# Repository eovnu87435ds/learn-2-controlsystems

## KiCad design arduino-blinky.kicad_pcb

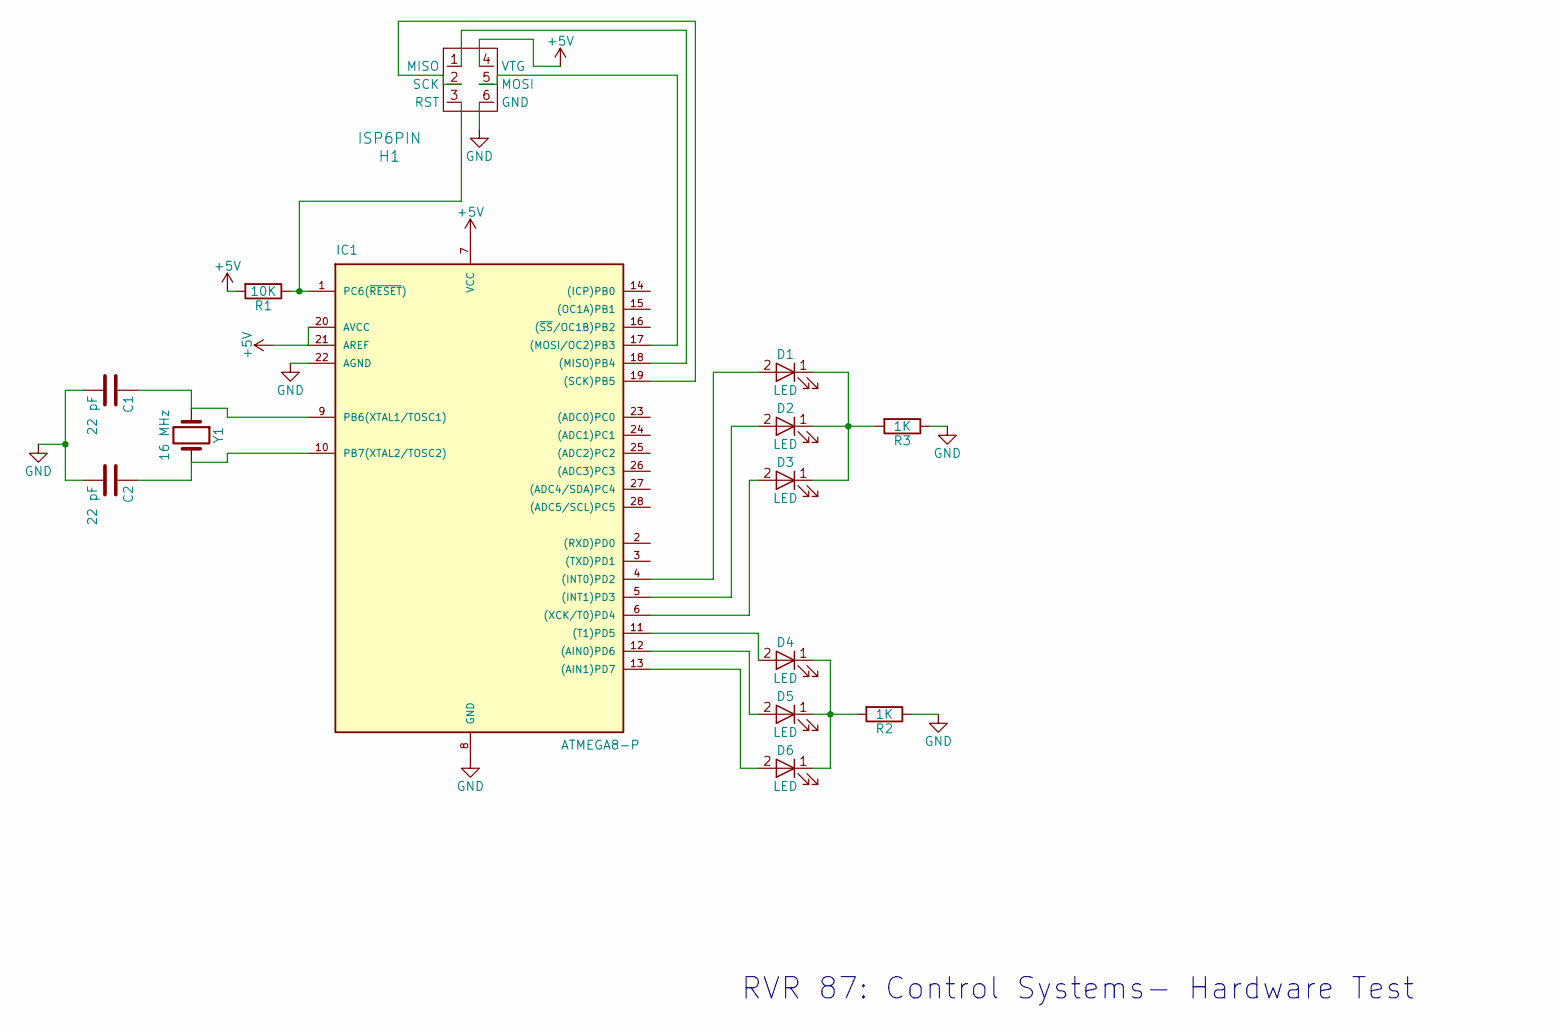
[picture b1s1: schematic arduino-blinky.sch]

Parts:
C1, C2: 22 pF; C_Disc_D3.0mm_W2.0mm_P2.50mm
D1, D2, D3, D4, D5, D6: LED; LED_D3.0mm
H1: ISP6PIN
IC1: ATMEGA8-P; DIP-28_W7.62mm_Socket
R1: 10K; R_Axial_DIN0309_L9.0mm_D3.2mm_P12.70mm_Horizontal
R2, R3: 1K; R_Axial_DIN0309_L9.0mm_D3.2mm_P12.70mm_Horizontal
Y1: 16 MHz; Crystal_HC18-U_Vertical

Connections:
+5V: H1.4 (VTG), IC1.7 (VCC), IC1.20 (AVCC), IC1.21 (AREF), R1.2
GND: C1.2, C2.2, H1.6 (GND), IC1.8 (GND), IC1.22 (AGND), R2.1, R3.1
unnamed: C1.1, IC1.9 (PB6(XTAL1/TOSC1)), Y1.1
unnamed: C2.1, IC1.10 (PB7(XTAL2/TOSC2)), Y1.2
unnamed: D1.1 (K), D2.1 (K), D3.1 (K), R3.2
unnamed: D1.2 (A), IC1.4 ((INT0)PD2)
unnamed: D2.2 (A), IC1.5 ((INT1)PD3)
unnamed: D3.2 (A), IC1.6 ((XCK/T0)PD4)
unnamed: D4.1 (K), D5.1 (K), D6.1 (K), R2.2
unnamed: D4.2 (A), IC1.11 ((T1)PD5)
unnamed: D5.2 (A), IC1.12 ((AIN0)PD6)
unnamed: D6.2 (A), IC1.13 ((AIN1)PD7)
unnamed: H1.1 (MISO), IC1.18 ((MISO)PB4)
unnamed: H1.2 (SCK), IC1.19 ((SCK)PB5)
unnamed: H1.3 (RST), IC1.1 (PC6(~RESET~)), R1.1
unnamed: H1.5 (MOSI), IC1.17 ((MOSI/OC2)PB3)

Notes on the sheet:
RVR 87: Control Systems- Hardware Test

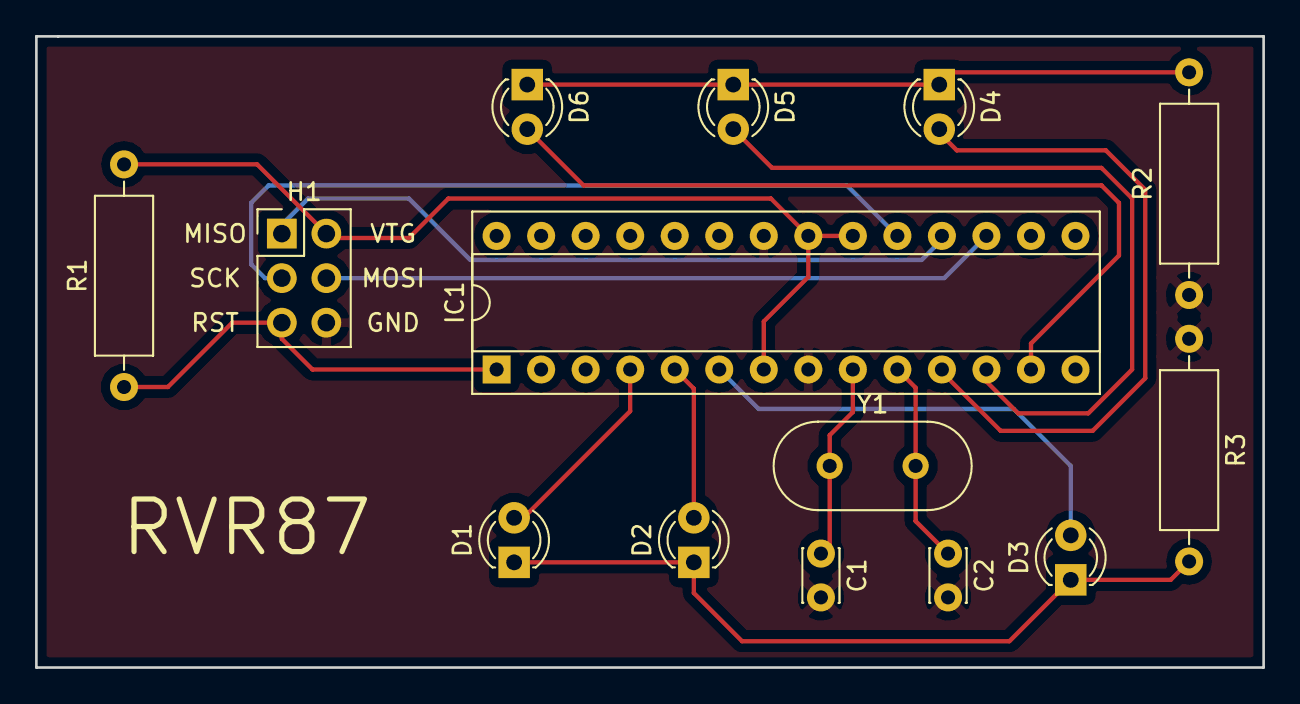
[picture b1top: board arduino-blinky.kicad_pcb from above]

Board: 2 copper layers, 70.0 x 36.0 mm, 14 parts (0 on the bottom side), 16 nets.

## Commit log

2017-03-09 Initial schematic work done
2017-03-09 PCB created
